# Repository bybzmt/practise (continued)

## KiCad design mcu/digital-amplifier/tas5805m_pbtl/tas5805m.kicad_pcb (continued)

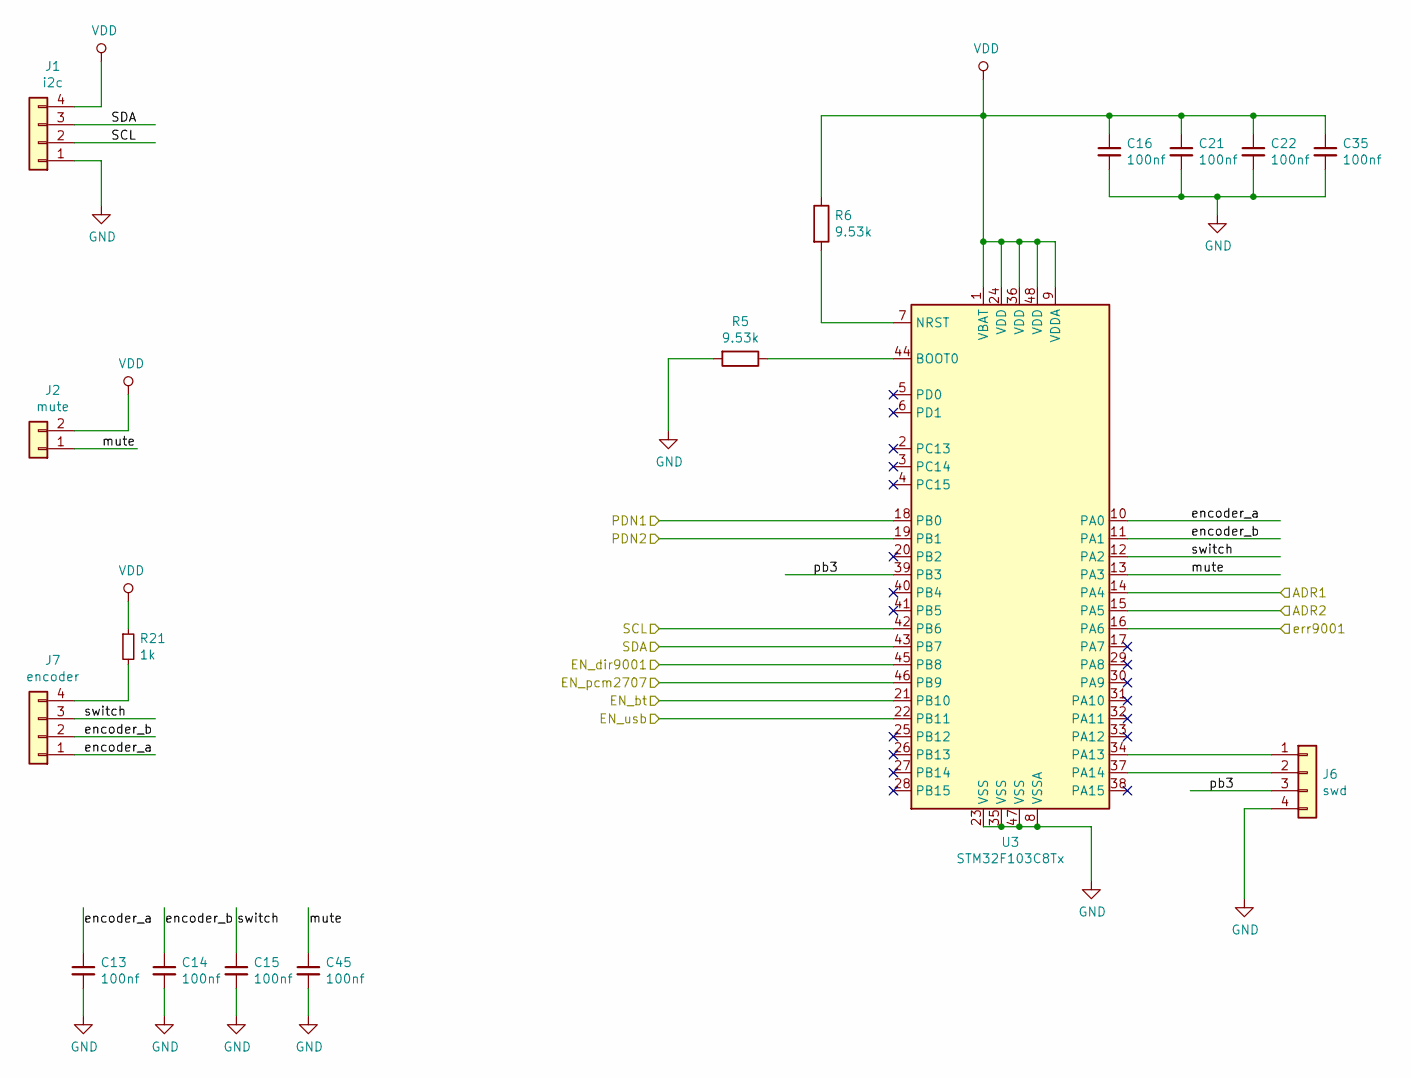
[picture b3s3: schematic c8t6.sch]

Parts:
C13, C14, C15, C16, C21, C22, C35, C45: 100nf; C_0805_2012Metric
J1: i2c; PinHeader_1x04_P2.54mm_Vertical
J2: mute; PinHeader_1x02_P2.54mm_Vertical
J6: swd; PinHeader_1x04_P2.54mm_Vertical
J7: encoder; PinHeader_1x04_P2.54mm_Vertical
R5, R6: 9.53k; R_0805_2012Metric
R21: 1k; R_0805_2012Metric
U3: STM32F103C8Tx; LQFP-48_7x7mm_P0.5mm

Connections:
/ADR1: U3.14 (PA4); also elsewhere on the board
/ADR2: U3.15 (PA5); also elsewhere on the board
/PDN1: U3.18 (PB0); also elsewhere on the board
/PDN2: U3.19 (PB1); also elsewhere on the board
/SCL: J1.2, U3.42 (PB6); also elsewhere on the board
/SDA: J1.3, U3.43 (PB7); also elsewhere on the board
/c8t6/encoder_a: C13.1, J7.1, U3.10 (PA0)
/c8t6/encoder_b: C14.1, J7.2, U3.11 (PA1)
/c8t6/mute: C45.1, J2.1, U3.13 (PA3)
/c8t6/pb3: J6.3, U3.39 (PB3)
/c8t6/switch: C15.1, J7.3, U3.12 (PA2)
/en9001: U3.45 (PB8); also elsewhere on the board
/en_bt: U3.21 (PB10); also elsewhere on the board
/en_usb: U3.22 (PB11); also elsewhere on the board
/err9001: U3.16 (PA6); also elsewhere on the board
/pcm2707: U3.46 (PB9); also elsewhere on the board
GND: C13.2, C14.2, C15.2, C16.2, C21.2, C22.2, C35.2, C45.2, J1.1, J6.4, R5.2, U3.8 (VSSA), U3.23 (VSS), U3.35 (VSS), U3.47 (VSS); also elsewhere on the board
unnamed: J6.1, U3.34 (PA13)
unnamed: J6.2, U3.37 (PA14)
unnamed: J7.4, R21.2
unnamed: R5.1, U3.44 (BOOT0)
unnamed: R6.2, U3.7 (NRST)
VDD: C16.1, C21.1, C22.1, C35.1, J1.4, J2.2, R6.1, R21.1, U3.1 (VBAT), U3.9 (VDDA), U3.24 (VDD), U3.36 (VDD), U3.48 (VDD); also elsewhere on the board

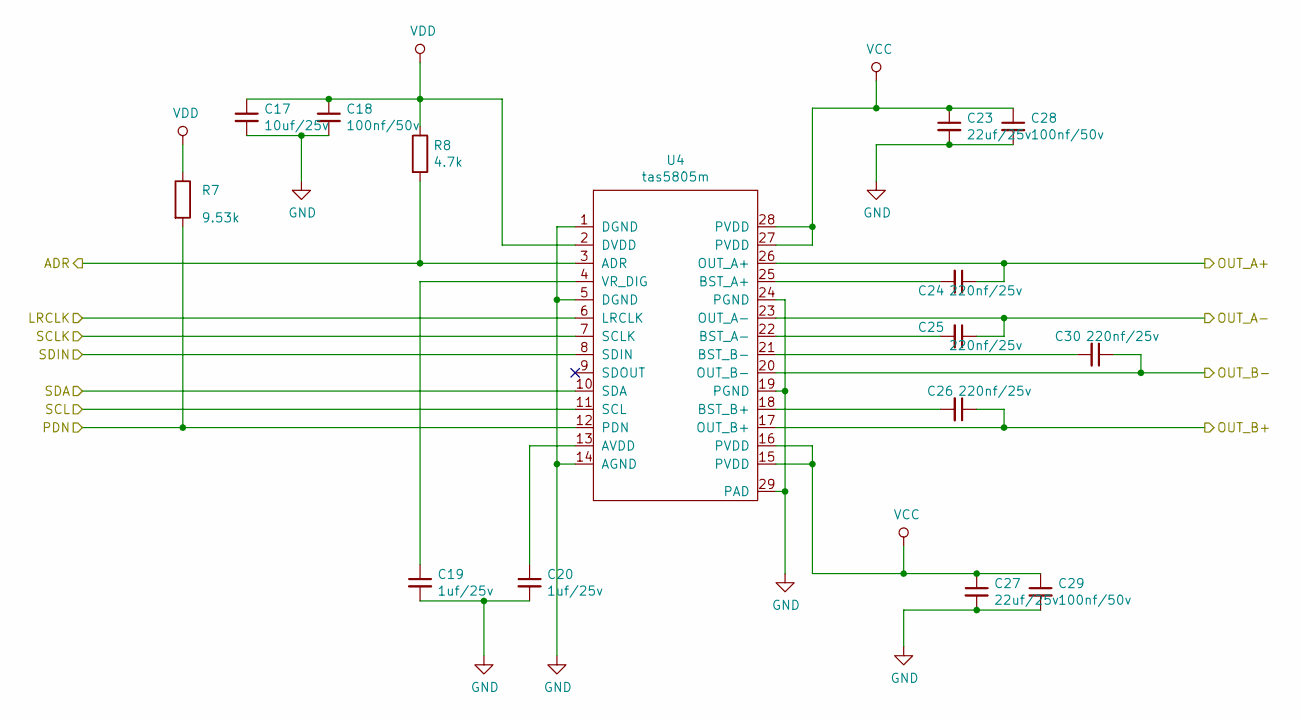
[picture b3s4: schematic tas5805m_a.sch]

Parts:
C17: 10uf/25v; C_0805_2012Metric
C18, C28, C29: 100nf/50v; C_0805_2012Metric
C19, C20: 1uf/25v; C_0805_2012Metric
C23, C27: 22uf/25v; C_0805_2012Metric
C24, C25, C26, C30: 220nf/25v; C_0603_1608Metric
R7: 9.53k; R_0805_2012Metric
R8: 4.7k; R_0805_2012Metric
U4: tas5805m; HTSSOP-28-1EP_4.4x9.7mm_P0.65mm_EP3.4x9.5mm

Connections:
/ADR1: R8.2, U4.3 (ADR); also elsewhere on the board
/LRCLK: U4.6 (LRCLK); also elsewhere on the board
/PDN1: R7.2, U4.12 (PDN); also elsewhere on the board
/SCL: U4.11 (SCL); also elsewhere on the board
/SCLK: U4.7 (SCLK); also elsewhere on the board
/SDA: U4.10 (SDA); also elsewhere on the board
/SDIN: U4.8 (SDIN); also elsewhere on the board
/tas5805m_a/OUT_A+: C24.1, C25.1, U4.23 (OUT_A-), U4.26 (OUT_A+); also elsewhere on the board
/tas5805m_a/OUT_B+: C26.1, C30.1, U4.17 (OUT_B+), U4.20 (OUT_B-); also elsewhere on the board
GND: C17.2, C18.2, C19.2, C20.2, C23.2, C27.2, C28.2, C29.2, U4.1 (DGND), U4.5 (DGND), U4.14 (AGND), U4.19 (PGND), U4.24 (PGND), U4.29 (PAD); also elsewhere on the board
unnamed: C19.1, U4.4 (VR_DIG)
unnamed: C20.1, U4.13 (AVDD)
unnamed: C24.2, U4.25 (BST_A+)
unnamed: C25.2, U4.22 (BST_A-)
unnamed: C26.2, U4.18 (BST_B+)
unnamed: C30.2, U4.21 (BST_B-)
VCC: C23.1, C27.1, C28.1, C29.1, U4.15 (PVDD), U4.16 (PVDD), U4.27 (PVDD), U4.28 (PVDD); also elsewhere on the board
VDD: C17.1, C18.1, R7.1, R8.1, U4.2 (DVDD); also elsewhere on the board

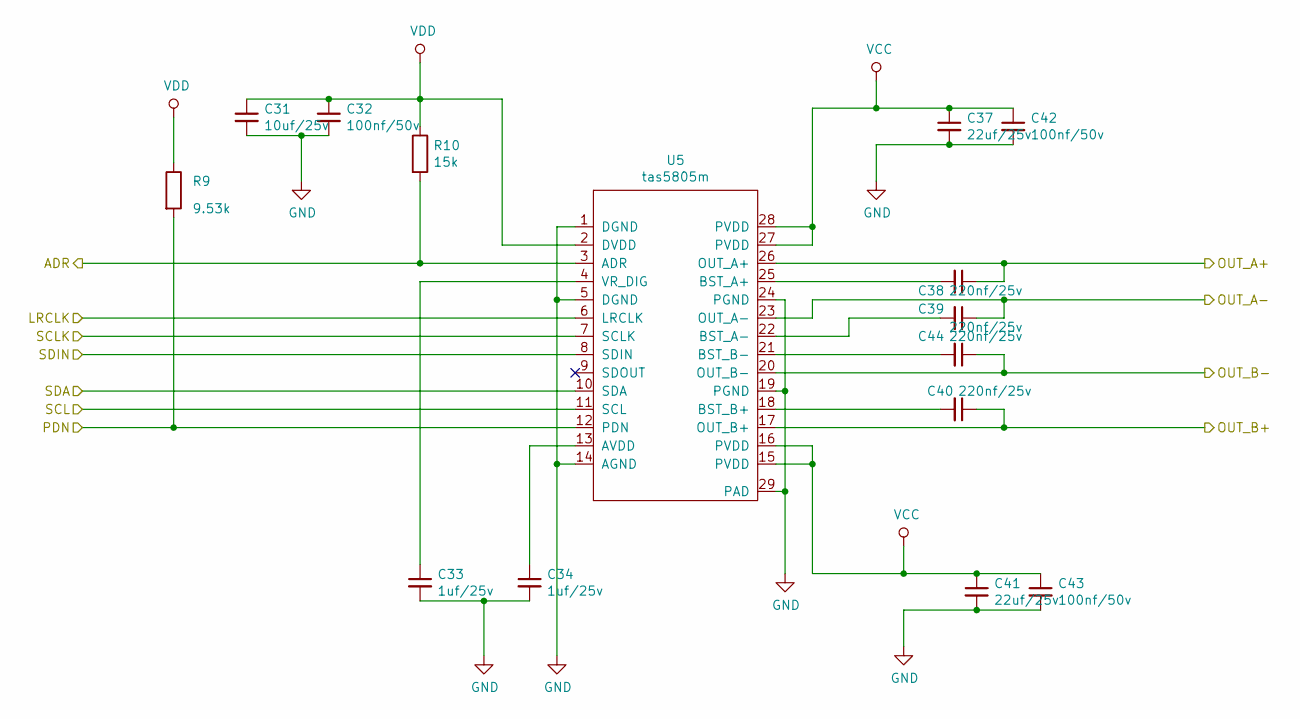
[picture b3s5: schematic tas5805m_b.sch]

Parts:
C31: 10uf/25v; C_0805_2012Metric
C32, C42, C43: 100nf/50v; C_0805_2012Metric
C33, C34: 1uf/25v; C_0805_2012Metric
C37, C41: 22uf/25v; C_0805_2012Metric
C38, C39, C40, C44: 220nf/25v; C_0603_1608Metric
R9: 9.53k; R_0805_2012Metric
R10: 15k; R_0805_2012Metric
U5: tas5805m; HTSSOP-28-1EP_4.4x9.7mm_P0.65mm_EP3.4x9.5mm

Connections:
/ADR2: R10.2, U5.3 (ADR); also elsewhere on the board
/LRCLK: U5.6 (LRCLK); also elsewhere on the board
/PDN2: R9.2, U5.12 (PDN); also elsewhere on the board
/SCL: U5.11 (SCL); also elsewhere on the board
/SCLK: U5.7 (SCLK); also elsewhere on the board
/SDA: U5.10 (SDA); also elsewhere on the board
/SDIN: U5.8 (SDIN); also elsewhere on the board
/tas5805m_b/OUT_A+: C38.1, C39.1, U5.23 (OUT_A-), U5.26 (OUT_A+); also elsewhere on the board
/tas5805m_b/OUT_B+: C40.1, C44.1, U5.17 (OUT_B+), U5.20 (OUT_B-); also elsewhere on the board
GND: C31.2, C32.2, C33.2, C34.2, C37.2, C41.2, C42.2, C43.2, U5.1 (DGND), U5.5 (DGND), U5.14 (AGND), U5.19 (PGND), U5.24 (PGND), U5.29 (PAD); also elsewhere on the board
unnamed: C33.1, U5.4 (VR_DIG)
unnamed: C34.1, U5.13 (AVDD)
unnamed: C38.2, U5.25 (BST_A+)
unnamed: C39.2, U5.22 (BST_A-)
unnamed: C40.2, U5.18 (BST_B+)
unnamed: C44.2, U5.21 (BST_B-)
VCC: C37.1, C41.1, C42.1, C43.1, U5.15 (PVDD), U5.16 (PVDD), U5.27 (PVDD), U5.28 (PVDD); also elsewhere on the board
VDD: C31.1, C32.1, R9.1, R10.1, U5.2 (DVDD); also elsewhere on the board

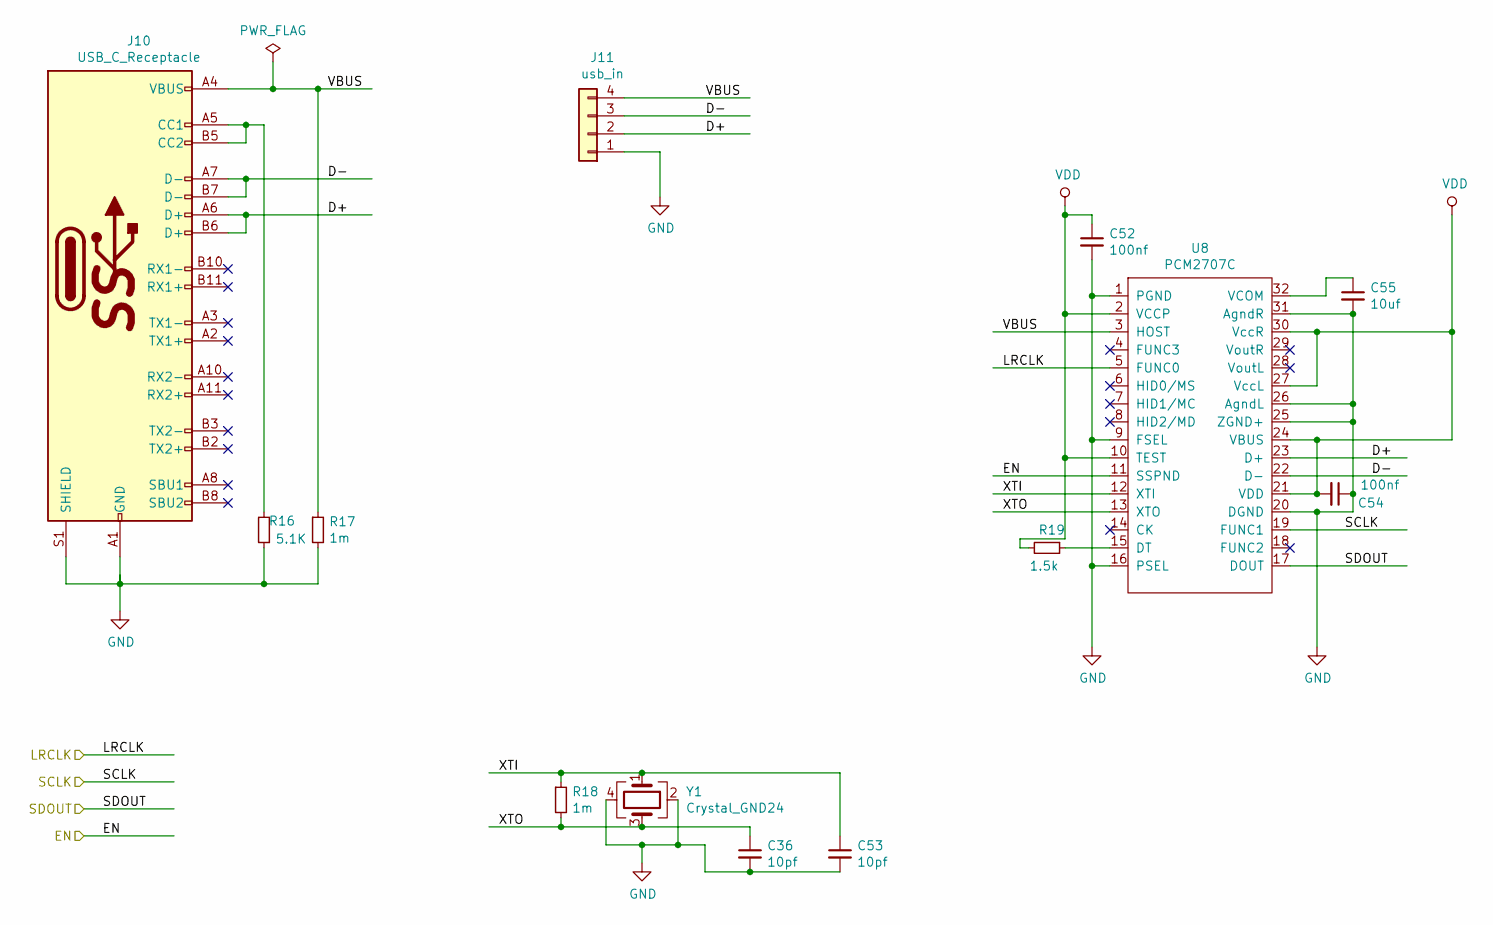
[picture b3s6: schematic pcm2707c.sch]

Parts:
C36, C53: 10pf; C_0805_2012Metric
C52, C54: 100nf; C_0805_2012Metric
C55: 10uf; C_0805_2012Metric
J10: USB_C_Receptacle; usb_c_24p_smd
J11: usb_in; PinSocket_1x04_P2.54mm_Vertical
R16: 5.1K; R_0805_2012Metric
R17, R18: 1m; R_0805_2012Metric
R19: 1.5k; R_0805_2012Metric
U8: PCM2707C; TQFP-32_7x7mm_P0.8mm
Y1: Crystal_GND24; Crystal_SMD_3225-4Pin_3.2x2.5mm

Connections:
/LRCLK: U8.5 (FUNC0); also elsewhere on the board
/SCLK: U8.19 (FUNC1); also elsewhere on the board
/SDIN: U8.17 (DOUT); also elsewhere on the board
/pcm2707: U8.11 (SSPND); also elsewhere on the board
/pcm2707c/D+: J10.A6 (D+), J10.B6 (D+), J11.2, U8.23 (D+)
/pcm2707c/D-: J10.A7 (D-), J10.B7 (D-), J11.3, U8.22 (D-)
/pcm2707c/VBUS: J10.A4 (VBUS), J10.A9 (VBUS), J10.B4 (VBUS), J10.B9 (VBUS), J11.4, R17.1, U8.3 (HOST)
/pcm2707c/XTI: C53.1, R18.1, U8.12 (XTI), Y1.1
/pcm2707c/XTO: C36.1, R18.2, U8.13 (XTO), Y1.3
GND: C36.2, C52.2, C53.2, C54.1, C55.2, J10.A1 (GND), J10.A12 (GND), J10.B1 (GND), J10.B12 (GND), J10.S1 (SHIELD), J11.1, R16.1, R17.2, U8.1 (PGND), U8.9 (FSEL), U8.16 (PSEL), U8.20 (DGND), U8.25 (ZGND+), U8.26 (AgndL), U8.31 (AgndR), Y1.2, Y1.4; also elsewhere on the board
unnamed: C55.1, U8.32 (VCOM)
unnamed: J10.A5 (CC1), J10.B5 (CC2), R16.2
unnamed: R19.1, U8.15 (DT)
VDD: C52.1, C54.2, R19.2, U8.2 (VCCP), U8.10 (TEST), U8.21 (VDD), U8.24 (VBUS), U8.27 (VccL), U8.30 (VccR); also elsewhere on the board

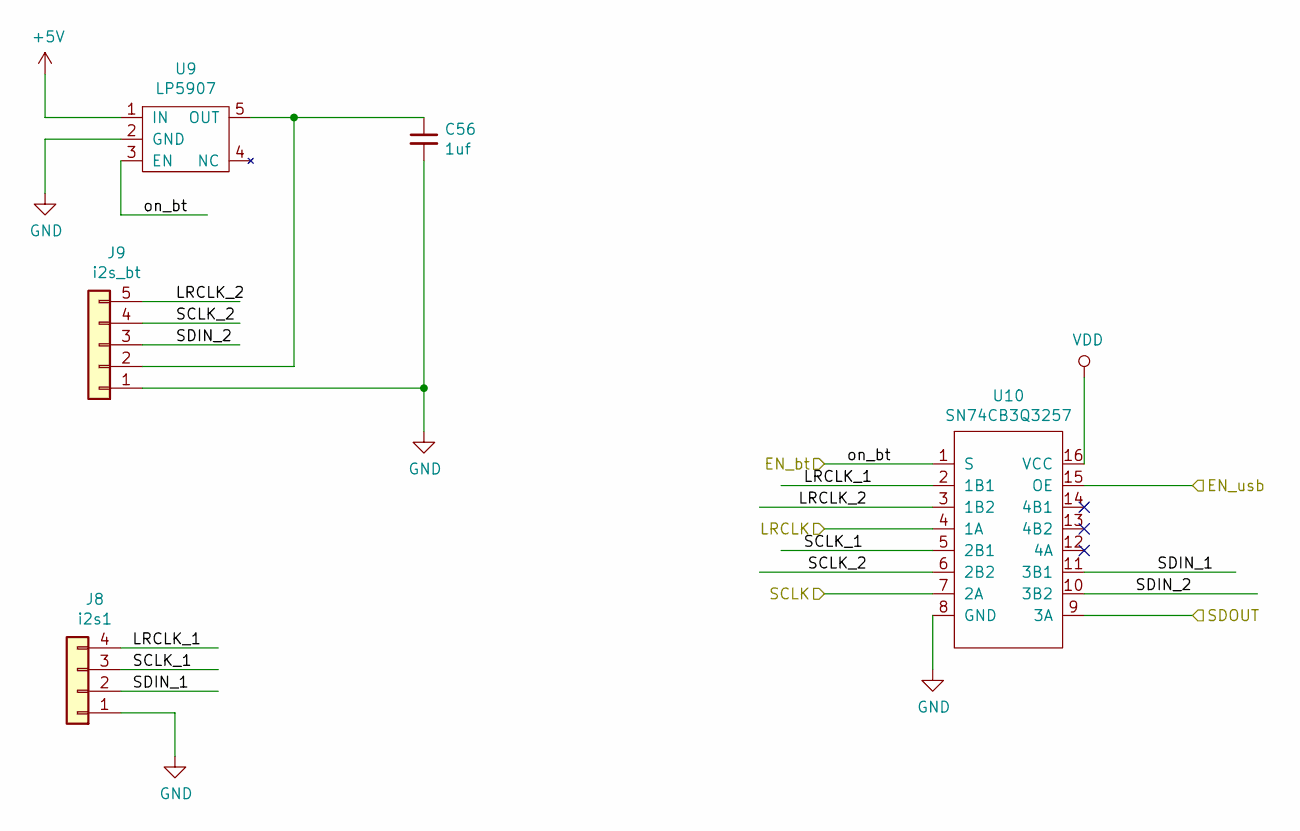
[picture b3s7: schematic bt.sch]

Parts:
C56: 1uf; C_0805_2012Metric
J8: i2s1; PinHeader_1x04_P2.54mm_Vertical
J9: i2s_bt; PinHeader_1x05_P2.54mm_Vertical
U9: LP5907; SOT-23-5
U10: SN74CB3Q3257; TSSOP-16_4.4x5mm_P0.65mm

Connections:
+5V: U9.1 (IN); also elsewhere on the board
/LRCLK: U10.4 (1A); also elsewhere on the board
/SCLK: U10.7 (2A); also elsewhere on the board
/SDIN: U10.9 (3A); also elsewhere on the board
/bt/LRCLK_1: J8.4, U10.2 (1B1)
/bt/LRCLK_2: J9.5, U10.3 (1B2)
/bt/SCLK_1: J8.3, U10.5 (2B1)
/bt/SCLK_2: J9.4, U10.6 (2B2)
/bt/SDIN_1: J8.2, U10.11 (3B1)
/bt/SDIN_2: J9.3, U10.10 (3B2)
/en_bt: U9.3 (EN), U10.1 (S); also elsewhere on the board
/en_usb: U10.15 (OE); also elsewhere on the board
GND: C56.2, J8.1, J9.1, U9.2 (GND), U10.8 (GND); also elsewhere on the board
unnamed: C56.1, J9.2, U9.5 (OUT)
VDD: U10.16 (VCC); also elsewhere on the board

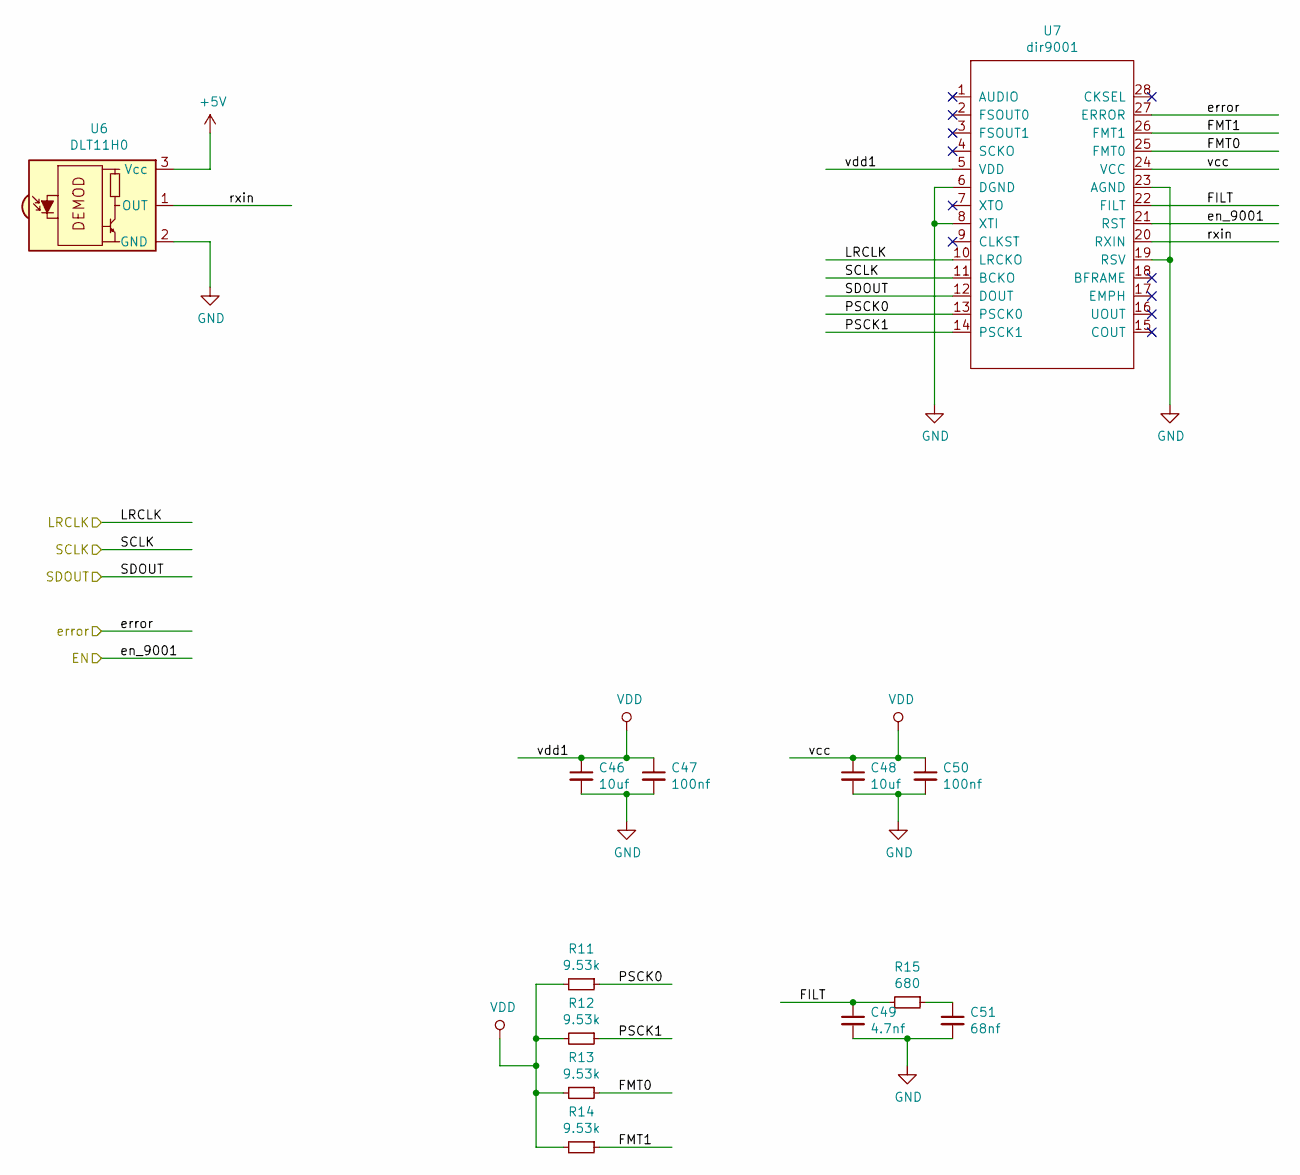
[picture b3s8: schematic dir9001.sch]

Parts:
C46, C48: 10uf; C_0805_2012Metric
C47, C50: 100nf; C_0805_2012Metric
C49: 4.7nf; C_0805_2012Metric
C51: 68nf; C_0805_2012Metric
R11, R12, R13, R14: 9.53k; R_0805_2012Metric
R15: 680; R_0805_2012Metric
U6: DLT11H0; spdif-DLT11H0
U7: dir9001; TSSOP-28_4.4x9.7mm_P0.65mm

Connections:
+5V: U6.3 (Vcc); also elsewhere on the board
/LRCLK: U7.10 (LRCKO); also elsewhere on the board
/SCLK: U7.11 (BCKO); also elsewhere on the board
/SDIN: U7.12 (DOUT); also elsewhere on the board
/dir9001/FILT: C49.1, R15.2, U7.22 (FILT)
/dir9001/FMT0: R13.1, U7.25 (FMT0)
/dir9001/FMT1: R14.1, U7.26 (FMT1)
/dir9001/PSCK0: R11.1, U7.13 (PSCK0)
/dir9001/PSCK1: R12.1, U7.14 (PSCK1)
/dir9001/rxin: U6.1 (OUT), U7.20 (RXIN)
/en9001: U7.21 (RST); also elsewhere on the board
/err9001: U7.27 (ERROR); also elsewhere on the board
GND: C46.2, C47.2, C48.2, C49.2, C50.2, C51.2, U6.2 (GND), U7.6 (DGND), U7.8 (XTI), U7.19 (RSV), U7.23 (AGND); also elsewhere on the board
unnamed: C51.1, R15.1
VDD: C46.1, C47.1, C48.1, C50.1, R11.2, R12.2, R13.2, R14.2, U7.5 (VDD), U7.24 (VCC); also elsewhere on the board

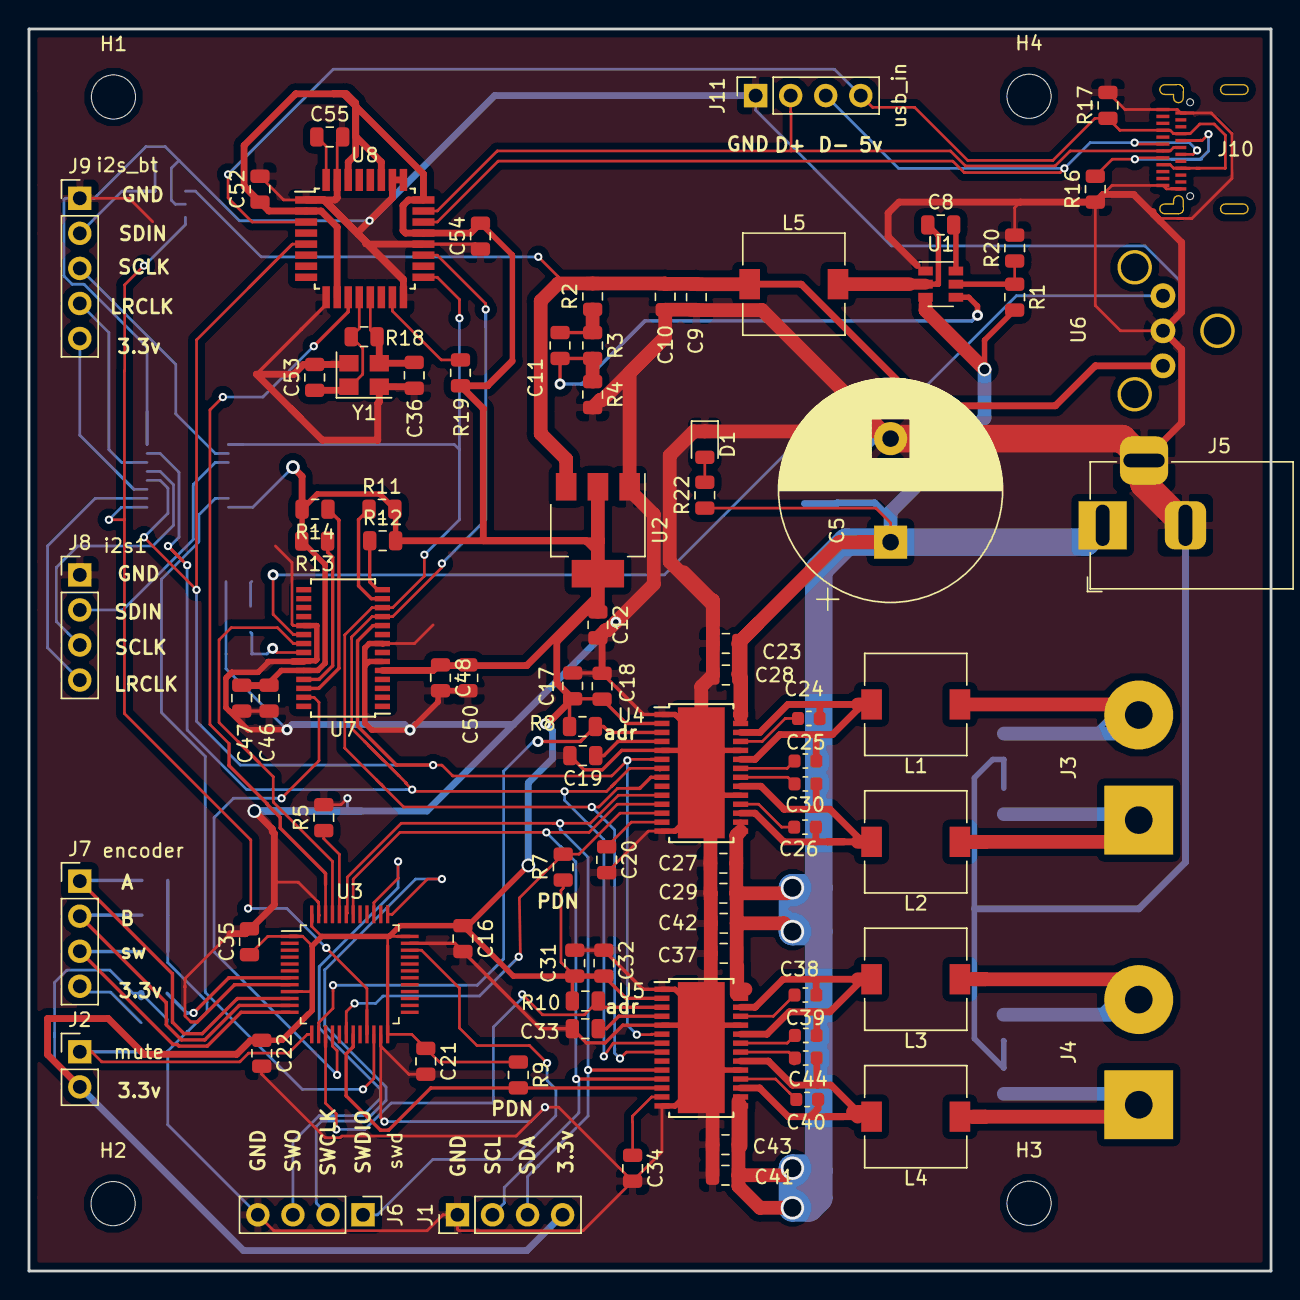
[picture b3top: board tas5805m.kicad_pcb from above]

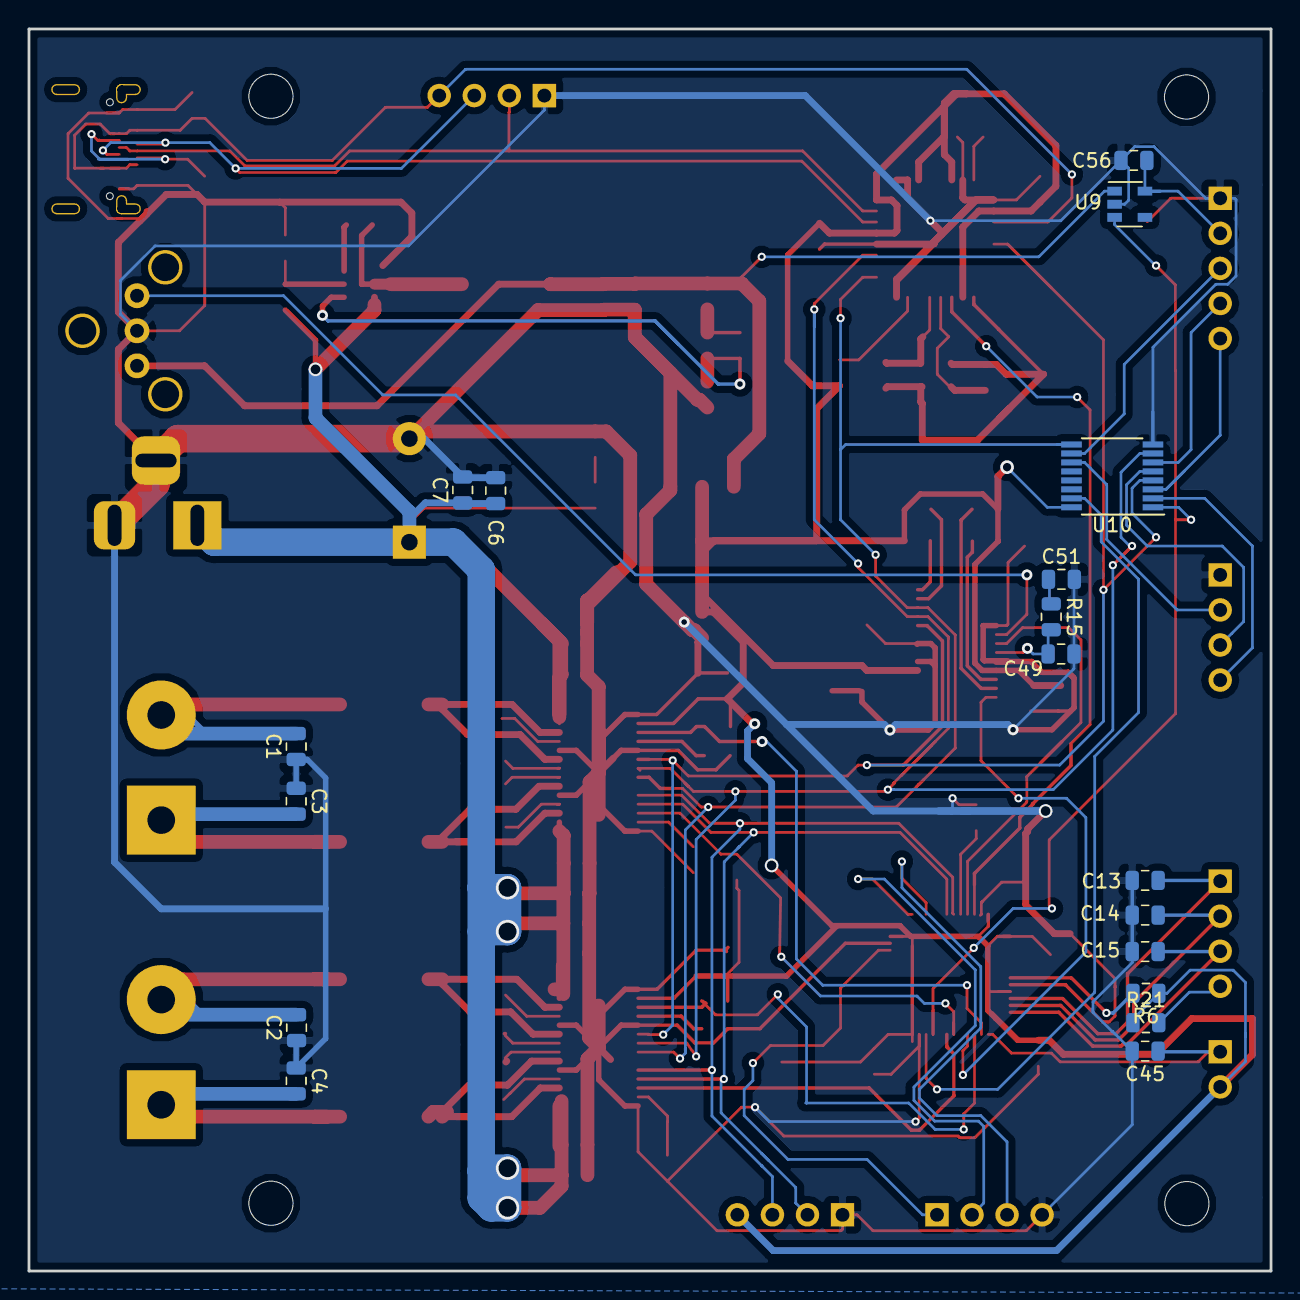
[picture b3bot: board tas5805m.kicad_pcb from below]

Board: 2 copper layers, 90.0 x 90.0 mm, 110 parts (18 on the bottom side), 76 nets.

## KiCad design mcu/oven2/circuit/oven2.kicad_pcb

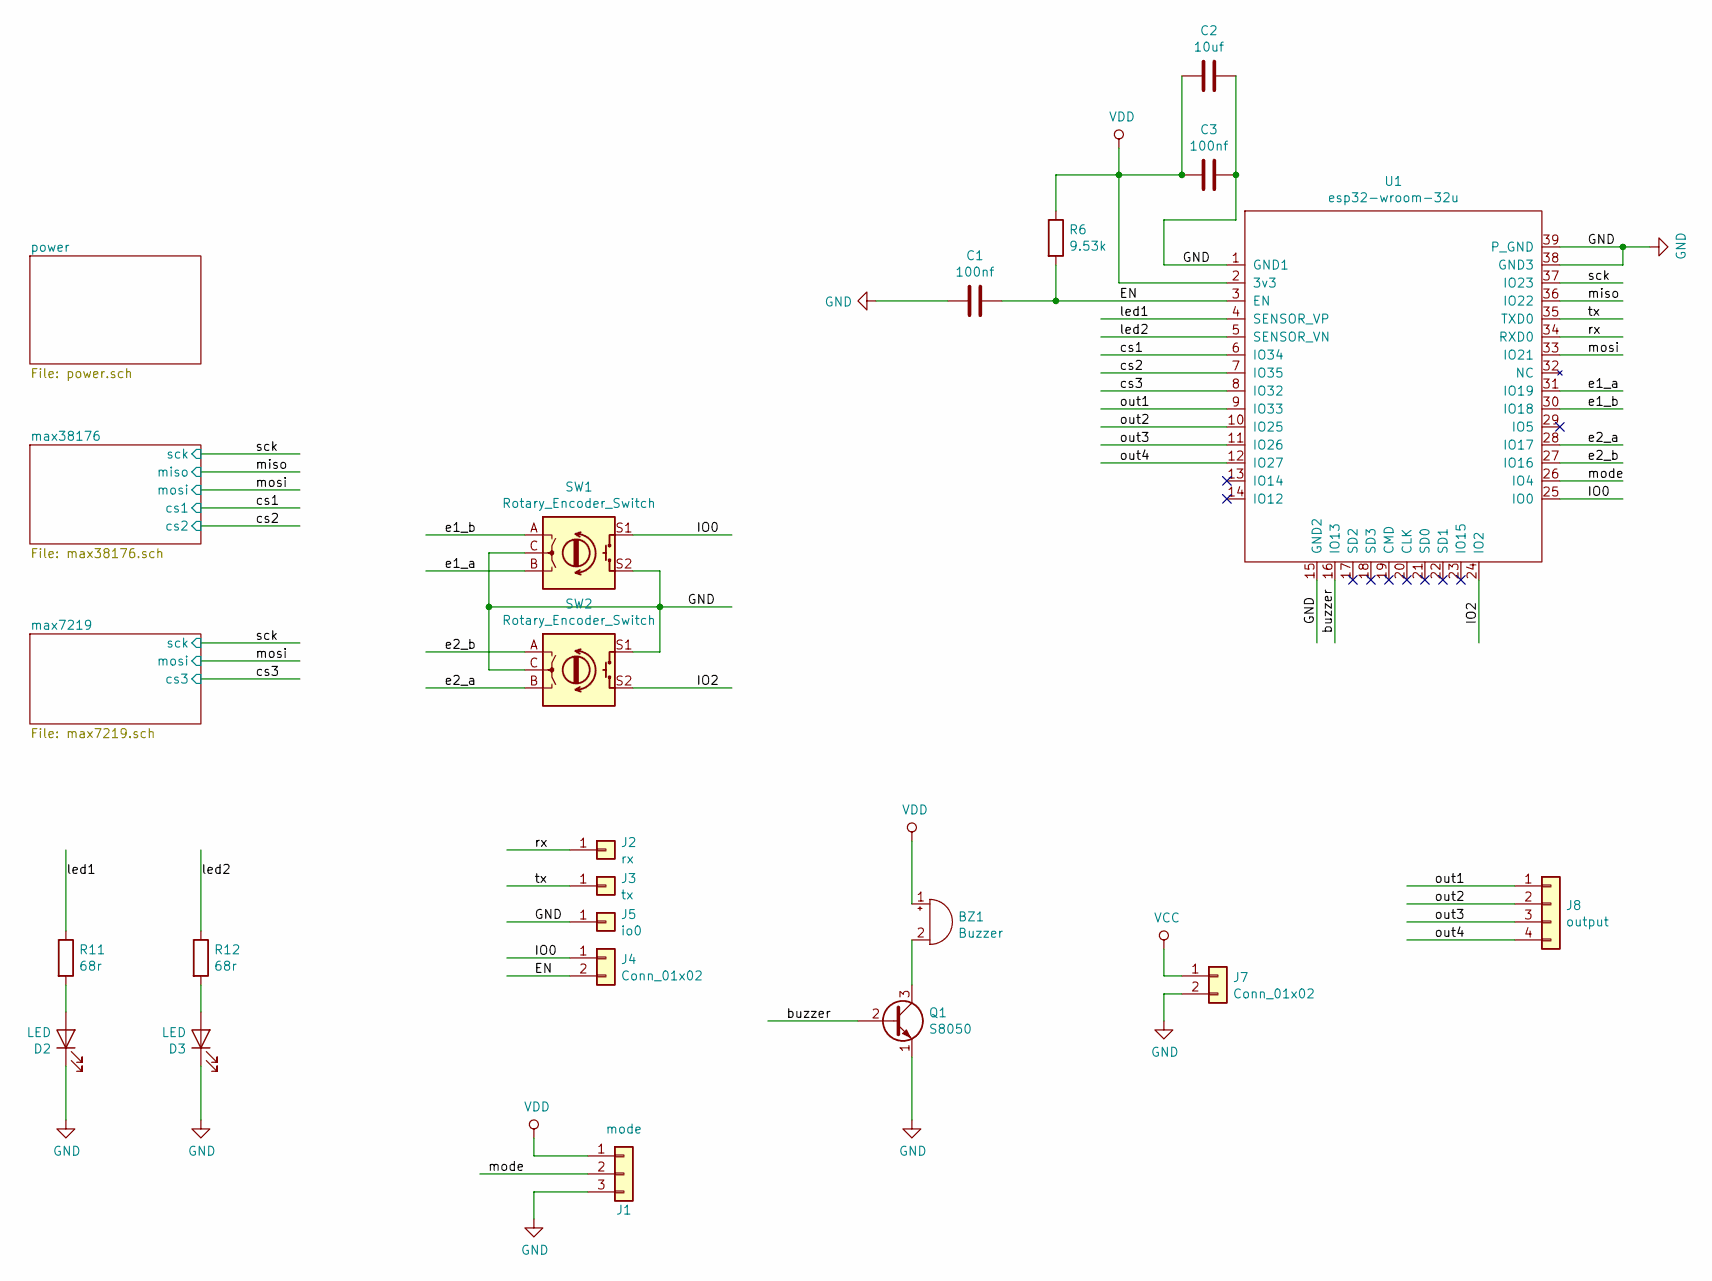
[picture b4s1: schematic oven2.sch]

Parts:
BZ1: Buzzer; Buzzer_12x9.5RM7.6
C1, C3: 100nf; C_0805_2012Metric
C2: 10uf; C_0805_2012Metric
D2, D3: LED; LED_D5.0mm
J1: mode; PinSocket_1x03_P2.54mm_Vertical
J2: rx; PinSocket_1x01_P2.54mm_Vertical
J3: tx; PinSocket_1x01_P2.54mm_Vertical
J4: Conn_01x02; PinHeader_1x02_P2.54mm_Vertical
J5: io0; PinSocket_1x01_P2.54mm_Vertical
J7: Conn_01x02; PinSocket_1x02_P2.54mm_Vertical
J8: output; PinHeader_1x04_P2.54mm_Vertical
Q1: S8050; SOT-23
R6: 9.53k; R_0805_2012Metric
R11, R12: 68r; R_0805_2012Metric
SW1, SW2: Rotary_Encoder_Switch; RotaryEncoder_Alps_EC11E-Switch_Vertical_H20mm
U1: esp32-wroom-32u

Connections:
/EN: C1.2, J4.2, R6.2, U1.3 (EN)
/IO0: J4.1, SW1.S1, U1.25 (IO0)
/IO2: SW2.S2, U1.24 (IO2)
/buzzer: Q1.2 (B), U1.16 (IO13)
/cs1: U1.6 (IO34); also elsewhere on the board
/cs2: U1.7 (IO35); also elsewhere on the board
/cs3: U1.8 (IO32); also elsewhere on the board
/e1_a: SW1.B, U1.31 (IO19)
/e1_b: SW1.A, U1.30 (IO18)
/e2_a: SW2.B, U1.28 (IO17)
/e2_b: SW2.A, U1.27 (IO16)
/led1: R11.1, U1.4 (SENSOR_VP)
/led2: R12.1, U1.5 (SENSOR_VN)
/miso: U1.36 (IO22); also elsewhere on the board
/mode: J1.2, U1.26 (IO4)
/mosi: U1.33 (IO21); also elsewhere on the board
/out1: J8.1, U1.9 (IO33)
/out2: J8.2, U1.10 (IO25)
/out3: J8.3, U1.11 (IO26)
/out4: J8.4, U1.12 (IO27)
/rx: J2.1, U1.34 (RXD0)
/sck: U1.37 (IO23); also elsewhere on the board
/tx: J3.1, U1.35 (TXD0)
GND: C1.1, C2.1, C3.2, D2.1 (K), D3.1 (K), J1.3, J5.1, J7.2, Q1.1 (E), SW1.C, SW1.S2, SW2.C, SW2.S1, U1.1 (GND1), U1.15 (GND2), U1.38 (GND3), U1.39 (P_GND); also elsewhere on the board
unnamed: BZ1.2 (+), Q1.3 (C)
unnamed: D2.2 (A), R11.2
unnamed: D3.2 (A), R12.2
VCC: J7.1; also elsewhere on the board
VDD: BZ1.1 (-), C2.2, C3.1, J1.1, R6.1, U1.2 (3v3); also elsewhere on the board

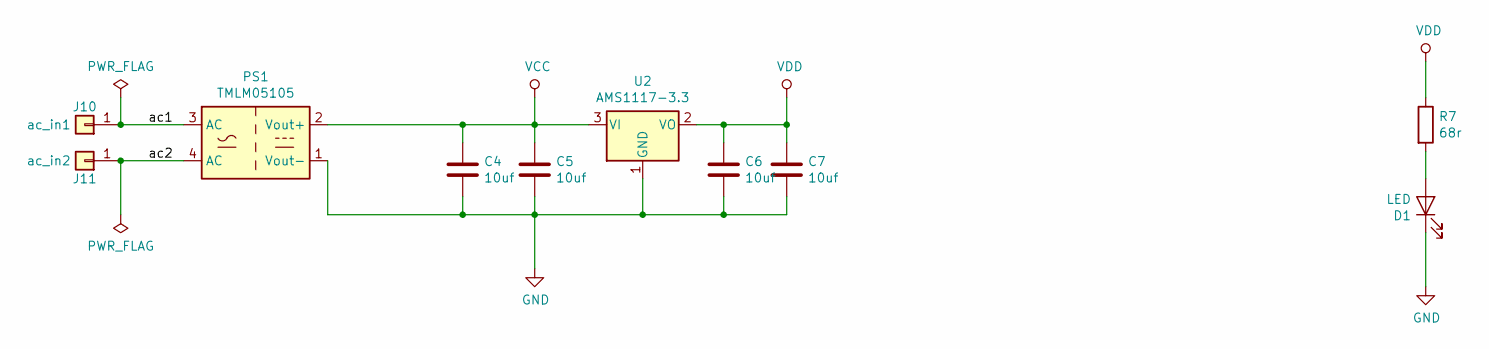
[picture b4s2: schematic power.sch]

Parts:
C4, C5, C6, C7: 10uf; C_0805_2012Metric
D1: LED; LED_D5.0mm
J10: ac_in1; 6.3mm
J11: ac_in2; 6.3mm
PS1: TMLM05105; HLK-5M05
R7: 68r; R_0805_2012Metric
U2: AMS1117-3.3; SOT-223-3_TabPin2

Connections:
/power/ac1: J10.1, PS1.3 (AC)
/power/ac2: J11.1, PS1.4 (AC)
GND: C4.2, C5.2, C6.2, C7.2, D1.1 (K), PS1.1 (Vout-), U2.1 (GND); also elsewhere on the board
unnamed: D1.2 (A), R7.2
VCC: C4.1, C5.1, PS1.2 (Vout+), U2.3 (VI); also elsewhere on the board
VDD: C6.1, C7.1, R7.1, U2.2 (VO); also elsewhere on the board

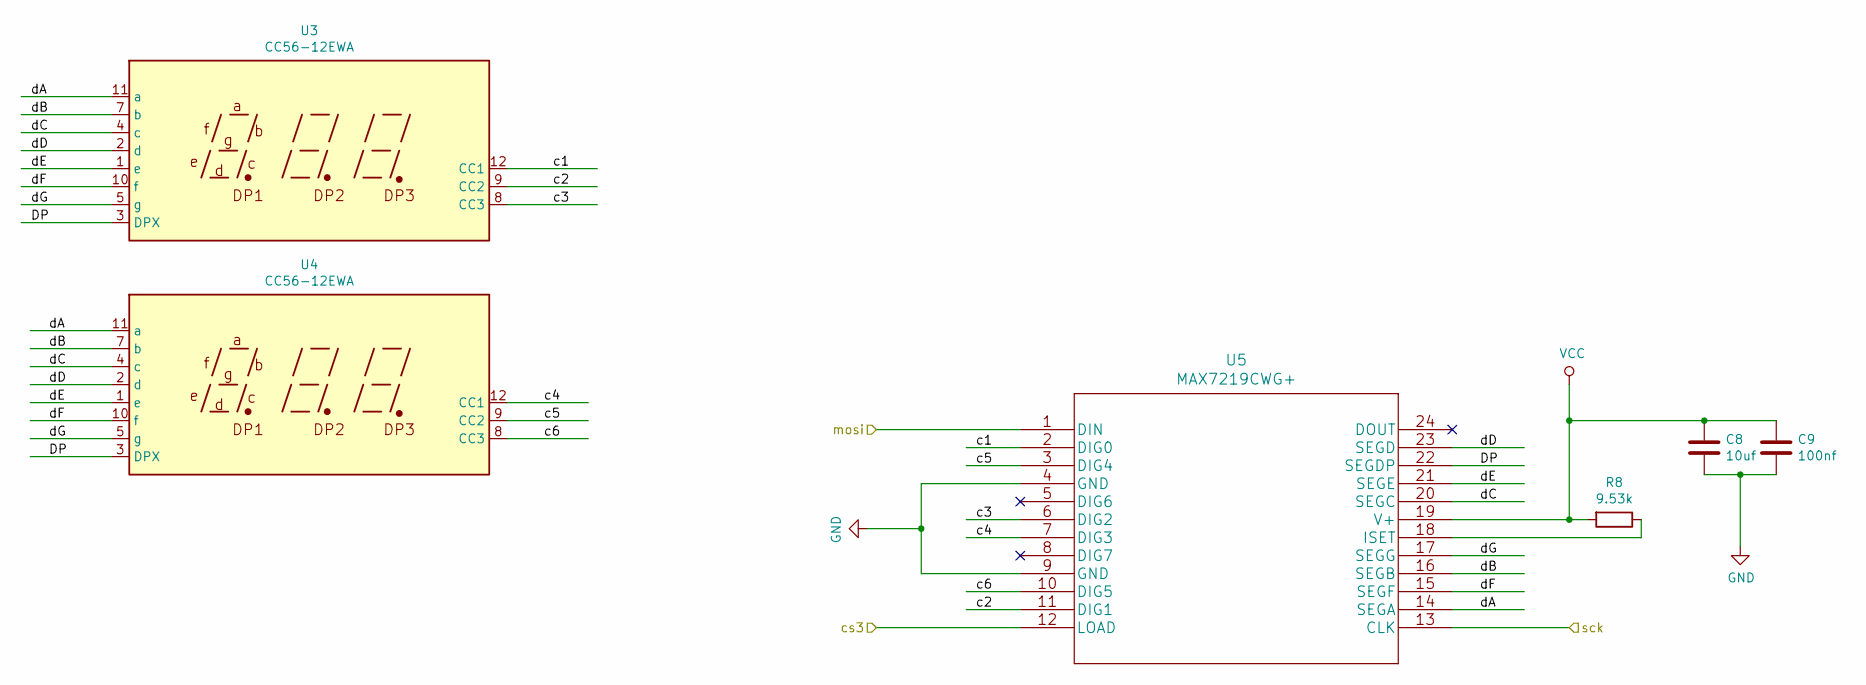
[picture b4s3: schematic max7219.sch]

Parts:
C8: 10uf; C_0805_2012Metric
C9: 100nf; C_0805_2012Metric
R8: 9.53k; R_0805_2012Metric
U3, U4: CC56-12EWA; 2831as
U5: MAX7219CWG+

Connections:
/cs3: U5.12 (LOAD); also elsewhere on the board
/max7219/DP: U3.3 (DPX), U4.3 (DPX), U5.22 (SEGDP)
/max7219/c1: U3.12 (CC1), U5.2 (DIG0)
/max7219/c2: U3.9 (CC2), U5.11 (DIG1)
/max7219/c3: U3.8 (CC3), U5.6 (DIG2)
/max7219/c4: U4.12 (CC1), U5.7 (DIG3)
/max7219/c5: U4.9 (CC2), U5.3 (DIG4)
/max7219/c6: U4.8 (CC3), U5.10 (DIG5)
/max7219/dA: U3.11 (a), U4.11 (a), U5.14 (SEGA)
/max7219/dB: U3.7 (b), U4.7 (b), U5.16 (SEGB)
/max7219/dC: U3.4 (c), U4.4 (c), U5.20 (SEGC)
/max7219/dD: U3.2 (d), U4.2 (d), U5.23 (SEGD)
/max7219/dE: U3.1 (e), U4.1 (e), U5.21 (SEGE)
/max7219/dF: U3.10 (f), U4.10 (f), U5.15 (SEGF)
/max7219/dG: U3.5 (g), U4.5 (g), U5.17 (SEGG)
/mosi: U5.1 (DIN); also elsewhere on the board
/sck: U5.13 (CLK); also elsewhere on the board
GND: C8.2, C9.2, U5.4 (GND), U5.9 (GND); also elsewhere on the board
unnamed: R8.1, U5.18 (ISET)
VCC: C8.1, C9.1, R8.2, U5.19 (V+); also elsewhere on the board
